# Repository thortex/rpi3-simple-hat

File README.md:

# 40-pin RPis Simple Hats

Simple Hats for 40-pin Raspbery Pi models.

## GPIO_LCD_HD44780

This hat includes the following devices:

1. three push switches.
2. three LEDs.
3. five DIP switches.
4. four I2C bus pin headers.
5. one HD44780-compatible LCD interface.
6. one CPU fan connector.
7. one UART bus pin header.

## HW-PWMx2
 
This hat includes the following interfaces:

1. Two hardware PWM controlled servo motor connectors.
2. A CPU fan connector.

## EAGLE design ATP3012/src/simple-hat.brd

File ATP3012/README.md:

# RPi から ATP3012 を制御するための基板

40-pin GPIO RPi から UART 経由で ATP3012 を制御するための基板です。

## 部品リスト

主要なものだけリストアップしています。抵抗・コンデンサは適当に揃えてください。

| 記号 | 説明         |  価格  | URL  | 
| ---- | ----         |  ----  | ---- |
| SV1  | 基板         |   \150 | http://akizukidenshi.com/catalog/g/gP-11073/ |
|      | コネクタ     |   \150 | http://akizukidenshi.com/catalog/g/gC-10702/ |
|      | DCジャック   |    \30 | http://akizukidenshi.com/catalog/g/gC-09408/ |
|      | 5V 4A 電源   | \1,000 | http://akizukidenshi.com/catalog/g/gM-06238/ |
|      | 5V 25mm Fan  |   \100 | http://akizukidenshi.com/catalog/g/gP-02480/ |
| IC1  | FXMA108      |   \250 | http://akizukidenshi.com/catalog/g/gM-04522/ |
|      | IC1 ソケット |   \100 | http://akizukidenshi.com/catalog/g/gP-00009/ |
| IC2  | ATP3012      |   \900 | http://akizukidenshi.com/catalog/g/gI-06218/ |
|      | または       |        | http://akizukidenshi.com/catalog/g/gI-09973/ |
|      | または       |        | http://akizukidenshi.com/catalog/g/gI-11517/ |
|      | IC2 ソケット |   \200 | http://akizukidenshi.com/catalog/g/gP-00013/ |
| Q4   | 2SA1015      |   \100 | http://akizukidenshi.com/catalog/g/gI-00882/ |
| SV2  | TPA2006      |   \300 | http://akizukidenshi.com/catalog/g/gK-08161/ |
|      | SV2 ソケット |    \30 | http://akizukidenshi.com/catalog/g/gC-03785/ |
| Q1   | 16 MHz発振子 |    \35 | http://akizukidenshi.com/catalog/g/gP-09576/ |
| R5   | 50k VR       |    \40 | http://akizukidenshi.com/catalog/g/gP-03281/ |

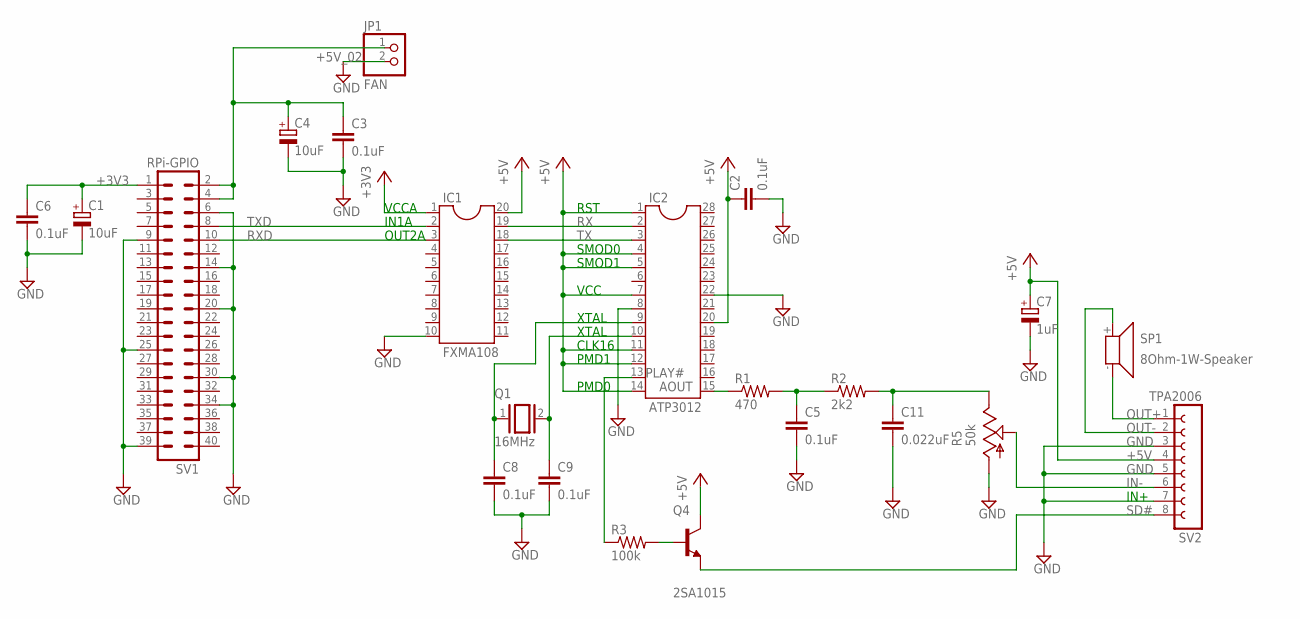
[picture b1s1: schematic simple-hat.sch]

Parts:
C1, C4: 10uF; E2-5
C2, C3, C5, C6, C8, C9: 0.1uF; C025-025X050
C7: 1uF; E5-10,5
C11: 0.022uF; C025-025X050
IC1: FXMA108; SOCKET-20
IC2: ATP3012; DIL28-4
JP1: FAN; 1X02
Q1: 16MHz; Q
Q4: 2SA1015; TO92-EBC
R1: 470; 0207/7
R2: 2k2; 0207/7
R3: 100k; 0207/7
R5: 50k; B25P
SP1: 8Ohm-1W-Speaker; SMS-1308MS-2-R
SV1: RPi-GPIO; MA20-2
SV2: TPA2006; FE08W

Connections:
+3V3: C1.+, C6.1, IC1.1, SV1.1
+5V: C2.1, C7.+, IC1.20, IC2.1, IC2.4, IC2.5, IC2.7, IC2.11, IC2.12, IC2.14, IC2.20, Q4.C, SV2.4
+5V_02: C3.1, C4.+, JP1.1, SV1.2, SV1.4
GND: C1.-, C2.2, C3.2, C4.-, C5.2, C6.2, C7.-, C8.2, C9.2, C11.2, IC1.10, IC2.8, IC2.22, JP1.2, R5.A, SV1.6, SV1.9, SV1.14, SV1.20, SV1.25, SV1.30, SV1.34, SV1.39, SV2.3, SV2.5, SV2.7
IN-: R5.S, SV2.6
unnamed: IC2.13, R3.1
unnamed: C9.1, IC2.10, Q1.2
unnamed: C8.1, IC2.9, Q1.1
unnamed: Q4.B, R3.2
unnamed: C5.1, R1.2, R2.1
unnamed: IC2.15, R1.1
unnamed: C11.1, R2.2, R5.E
OUT+: SP1.- (2), SV2.1
OUT-: SP1.+ (1), SV2.2
RX: IC1.19, IC2.2
RXD: IC1.3, SV1.10
SD#: Q4.E, SV2.8
TX: IC1.18, IC2.3
TXD: IC1.2, SV1.8

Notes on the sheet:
IN+
VCCA
IN1A
OUT2A
RST
SMOD0
SMOD1
VCC
XTAL
CLK16
PMD1
PMD0

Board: 2 copper layers, 22 parts (0 on the bottom side), 19 nets, no tracks yet.

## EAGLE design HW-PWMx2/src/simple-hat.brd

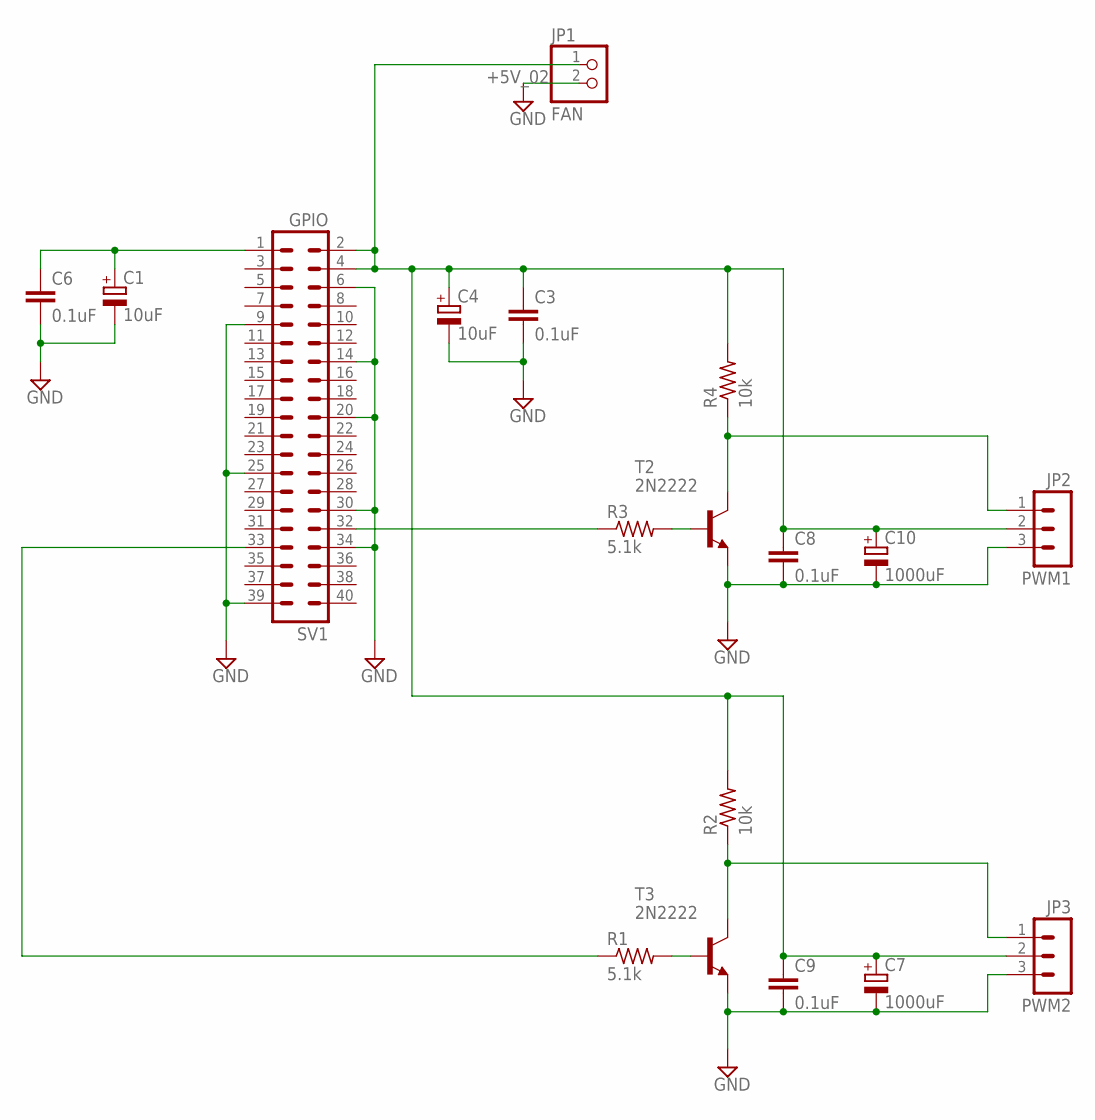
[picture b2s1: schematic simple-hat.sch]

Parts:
C1, C4: 10uF; E2-5
C3, C6, C8, C9: 0.1uF; C025-025X050
C7, C10: 1000uF; E5-10,5
JP1: FAN; 1X02
PWM1: JP2; MA03-1
PWM2: JP3; MA03-1
R1, R3: 5.1k; 0207/7
R2, R4: 10k; 0207/7
SV1: GPIO; MA20-2
T2, T3: 2N2222; TO92-EBC

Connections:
+5V_02: C3.1, C4.+, C7.+, C8.1, C9.1, C10.+, JP1.1, PWM1.2, PWM2.2, R2.2, R4.2, SV1.2, SV1.4
GND: C1.-, C3.2, C4.-, C6.2, C7.-, C8.2, C9.2, C10.-, JP1.2, PWM1.3, PWM2.3, SV1.6, SV1.9, SV1.14, SV1.20, SV1.25, SV1.30, SV1.34, SV1.39, T2.E, T3.E
unnamed: C1.+, C6.1, SV1.1
unnamed: R1.1, SV1.33
unnamed: R3.1, SV1.32
unnamed: R3.2, T2.B
unnamed: PWM1.1, R4.1, T2.C
unnamed: R1.2, T3.B
unnamed: PWM2.1, R2.1, T3.C

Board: 2 copper layers, 18 parts (0 on the bottom side), 9 nets, no tracks yet.

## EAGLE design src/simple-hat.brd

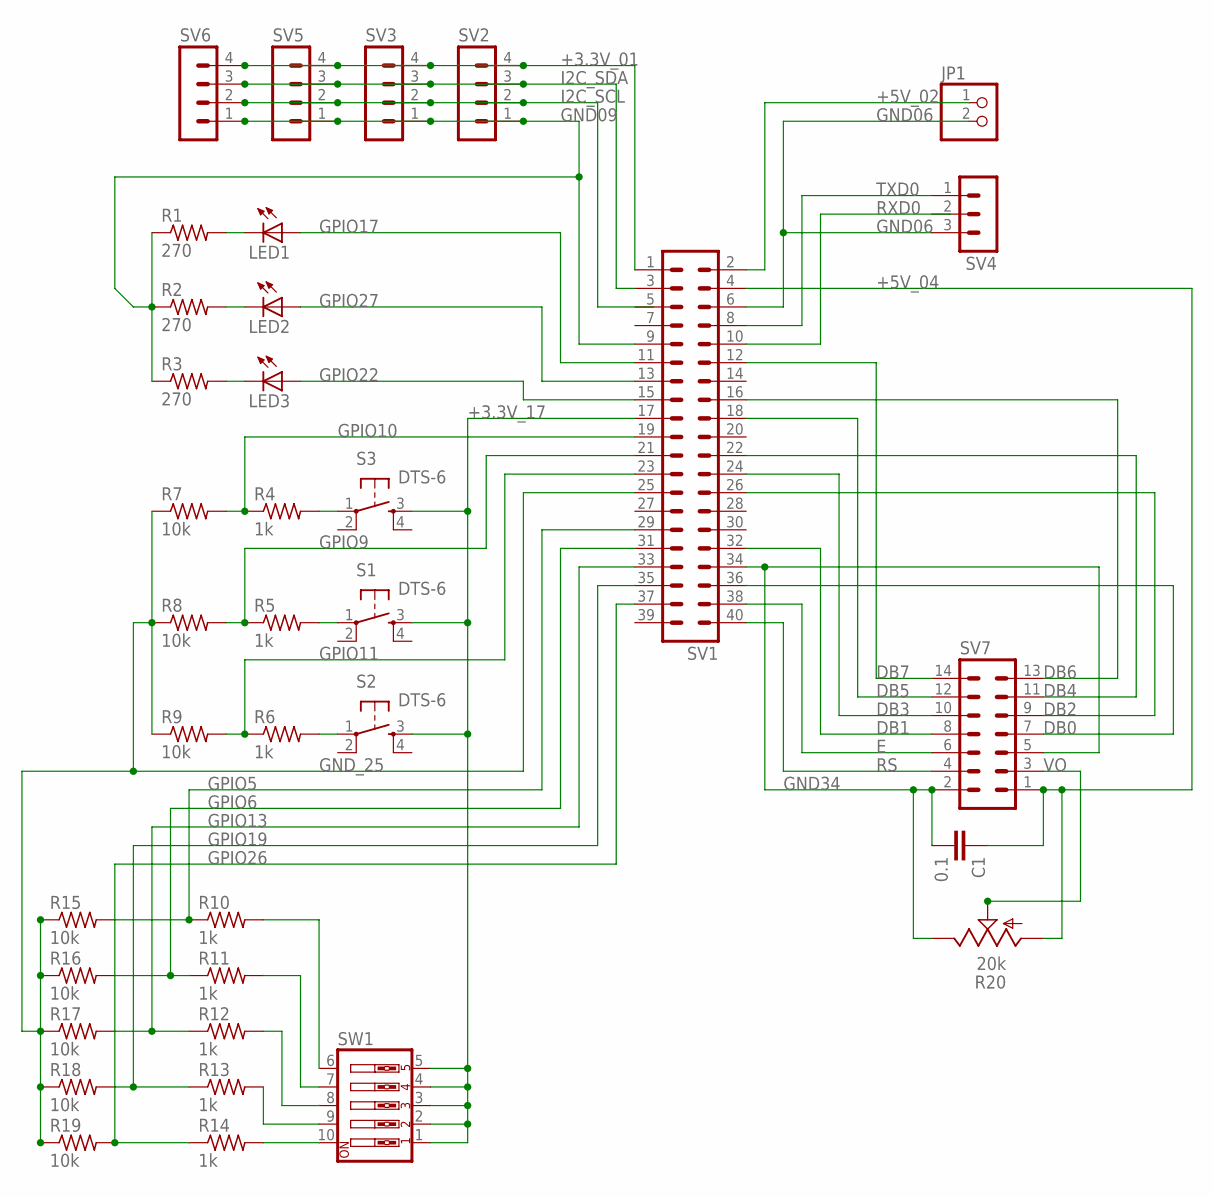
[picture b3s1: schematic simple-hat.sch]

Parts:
C1: 0.1; C050-025X075
JP1: PINHD-1X2; 1X02
LED1, LED2, LED3: LED3MM
R1, R2, R3: 270; 0207/7
R4, R5, R6, R10, R11, R12, R13, R14: 1k; 0207/7
R7, R8, R9, R15, R16, R17, R18, R19: 10k; 0207/7
R20: 20k; B25P
S1, S2, S3: DTS-6
SV1: MA20-2
SV2, SV3, SV5, SV6: MA04-1
SV4: MA03-1
SV7: MA07-2
SW1: SW_DIP-5; EDG-05

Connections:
+3.3V_01: SV1.1, SV2.4, SV3.4, SV5.4, SV6.4
+3.3V_17: S1.3, S2.3, S3.3, SV1.17, SW1.1, SW1.2, SW1.3, SW1.4, SW1.5
+5V_02: JP1.1, SV1.2
+5V_04: C1.1, R20.A, SV1.4, SV7.1
DB0: SV1.36, SV7.7
DB1: SV1.32, SV7.8
DB2: SV1.26, SV7.9
DB3: SV1.24, SV7.10
DB4: SV1.22, SV7.11
DB5: SV1.18, SV7.12
DB6: SV1.16, SV7.13
DB7: SV1.12, SV7.14
E: SV1.38, SV7.6
GND06: JP1.2, SV1.6, SV4.3
GND09: R1.1, R2.1, R3.1, SV1.9, SV2.1, SV3.1, SV5.1, SV6.1
GND34: C1.2, R20.E, SV1.34, SV7.2, SV7.5
GND_25: R7.1, R8.1, R9.1, R15.1, R16.1, R17.1, R18.1, R19.1, SV1.25
GPIO5: R10.1, R15.2, SV1.29
GPIO6: R11.1, R16.2, SV1.31
GPIO9: R5.1, R8.2, SV1.21
GPIO10: R4.1, R7.2, SV1.19
GPIO11: R6.1, R9.2, SV1.23
GPIO13: R12.1, R17.2, SV1.33
GPIO17: LED1.A, SV1.11
GPIO19: R13.1, R18.2, SV1.35
GPIO22: LED3.A, SV1.15
GPIO26: R14.1, R19.2, SV1.37
GPIO27: LED2.A, SV1.13
I2C_SCL: SV2.2, SV3.2, SV5.2, SV6.2
I2C_SDA: SV1.3, SV2.3, SV3.3, SV5.3, SV6.3
unnamed: LED1.K (C), R1.2
unnamed: LED2.K (C), R2.2
unnamed: LED3.K (C), R3.2
unnamed: R4.2, S3.1
unnamed: R5.2, S1.1
unnamed: R6.2, S2.1
unnamed: R11.2, SW1.7
unnamed: R12.2, SW1.8
unnamed: R10.2, SW1.6
unnamed: R13.2, SW1.9
unnamed: R14.2, SW1.10
RS: SV1.40, SV7.4
RXD0: SV1.10
TXD0: SV1.8, SV4.1
VO: R20.S, SV7.3

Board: 2 copper layers, 36 parts (0 on the bottom side), 44 nets, no tracks yet.

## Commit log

2016-07-24 Added v0.0.1
2016-07-27 Added routed borad data
2016-10-30 Created a sub-directory for GPIO LCD simple hat.
2016-11-19 2 channels Hardware PWM controlling board.
2016-11-24 Modified HW-PWMx2
2017-03-03 Modified GPIO_LCD circuit.
2017-03-03 Modified hardware PWM circuit.
2017-03-04 modified schematics pdf file.
2017-03-04 Added CPU Fan for AE-RPi
2017-03-11 Added RPi3-ATP3012 schem.
2017-03-11 Added README file.
2017-03-12 Added instruction images.
2017-04-08 Added AKIZUKI GPS.
2017-04-08 fixed typo.
2017-04-08 Modified README
2017-04-09 Modified README file.
2017-04-09 Added images.
2017-04-10 Modified README.
2017-04-15 Added descriptions of Navit Japanese tranlation file.
2017-04-19 bugfix: added mkdir command input.
2017-04-28 Added Navit Configurator.
